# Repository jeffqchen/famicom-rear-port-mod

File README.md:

# Famicom Rear Port Mod
The Nintendo Famicom has been nagging me for almost my whole life with its non-detachable controllers and awkward length of the cord. So here is the solution to scratch that itch.

3D model slicer examples as shown in the pictures for best appearance/structural strength.

To keep the original appearance with the controllers, you can replace the long wire from original Famicom controllers with a NES controller extension corder, cut into desired length.

2P microphone pin is populated on an N/C pin, if you want to use it, get a 7-pin zapper extension cord instead (pricier).

-----------
## Parts

- PCB
  - [1P](https://oshpark.com/shared_projects/gRNN75yp)
  - [2P](https://oshpark.com/shared_projects/Hxw588oo)

- [22x or 28x] Terminal Pins, Male, Machined - [Link](https://github.com/jeffqchen/JeffParts/blob/main/Connectors/Terminal%20Pins/Machined%20Male/info.md)

- 6-Conductor Ribbon Cable - [Link](https://github.com/jeffqchen/JeffParts/blob/main/Parts/Cables/Ribbon%20Cable/6-Conductor/info.md)

- M3 Hex Socket Head Cap Screws/Nuts Kit - [Link](https://github.com/jeffqchen/JeffParts/blob/main/Parts/M2%20M3%20Hex%20Screw%20%26%20Nut/info.md)

-----------
## Assembly

- You may need to file/cut/drill away any inaccuracies in order to fit the parts together correctly.

Soldering demonstration included in pictures.  
- Some pins are N/C so I didn't waste my money populating them.  
- Don't use too much solder since the space inside is pretty constrained.  
- Wire pinout is serialized. It should be very straightforward. Don't cross the streams!  
- Wire pin holes are also compatible with 2mm and 2.54mm pitched pins, if you prefer  
using pins for connection. Remember to cut the protruding from the other side or it won't fit.

-----------
Shield: [![CC BY-SA 4.0][cc-by-sa-shield]][cc-by-sa]

This work is licensed under a
[Creative Commons Attribution-ShareAlike 4.0 International License][cc-by-sa].

[![CC BY-SA 4.0][cc-by-sa-image]][cc-by-sa]

[cc-by-sa]: http://creativecommons.org/licenses/by-sa/4.0/
[cc-by-sa-image]: https://licensebuttons.net/l/by-sa/4.0/88x31.png
[cc-by-sa-shield]: https://img.shields.io/badge/License-CC%20BY--SA%204.0-lightgrey.svg

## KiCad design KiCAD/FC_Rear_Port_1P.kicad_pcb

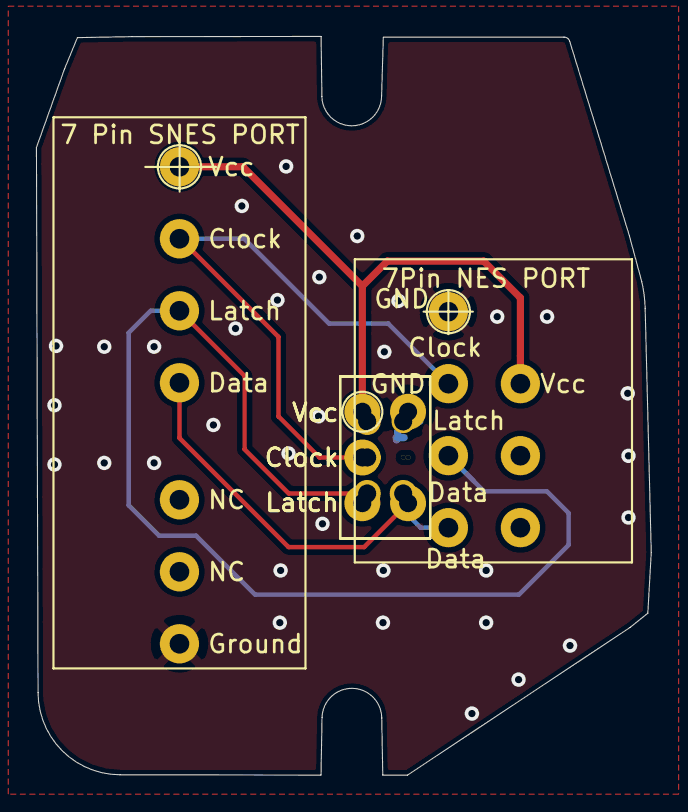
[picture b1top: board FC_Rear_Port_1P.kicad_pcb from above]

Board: 2 copper layers, 34.2 x 41.0 mm, 3 parts (0 on the bottom side), 5 nets.

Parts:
P1: NES_7P_PORT; 7_Pin_NES_Controller_Port
P2: SNES_7P_PORT; 7_Pin_SNES_Controller_Port
P3: FC_6P_CONN; 6_Pin_FC_Controller_Connection_2.54mm

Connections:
unnamed: P1.1, P2.7, P3.6
unnamed: P1.2, P2.2, P3.2
unnamed: P1.3, P2.3, P3.3
unnamed: P1.4, P2.4, P3.4
unnamed: P1.7, P2.1, P3.1

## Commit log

2020-11-03 Add existing files
2020-11-03 Remove useless files
2020-11-03 Add 3D files
2020-11-30 Improve 3D model for better insertion experience
2021-10-27 Create LICENSE
2022-08-09 Change license type
